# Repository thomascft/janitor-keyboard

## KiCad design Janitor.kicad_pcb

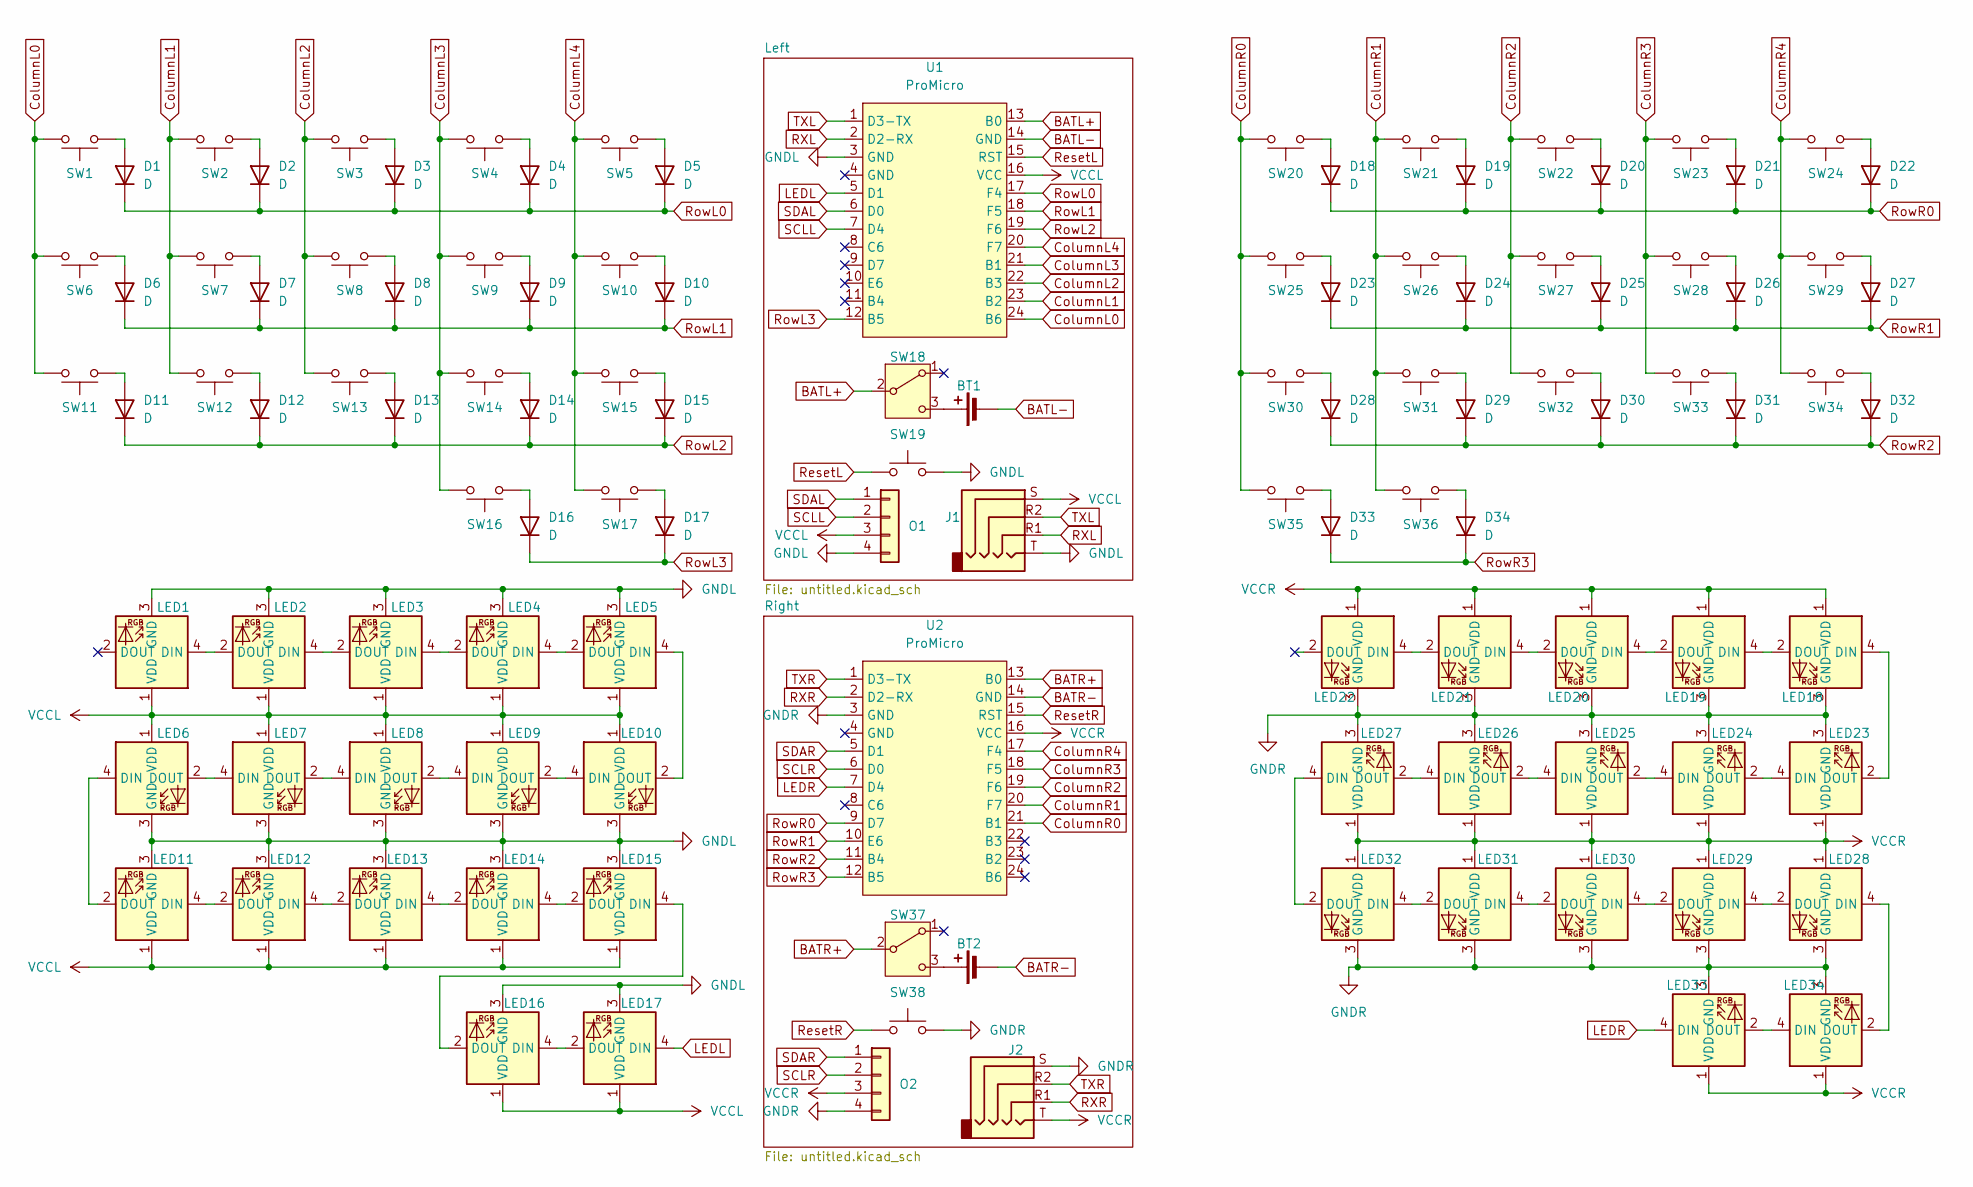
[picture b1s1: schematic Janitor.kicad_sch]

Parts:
BT1, BT2: Battery_Cell; CONN_Battery_JST
D1, D2, D3, D4, D5, D6, D7, D8, D9, D10, D11, D12, D13, D14, D15, D16, D17, D18, D19, D20, D21, D22, D23, D24, D25, D26, D27, D28, D29, D30, D31, D32, D33, D34: D; D_SOD-123
J1, J2: AudioJack4; TRRS-PJ-320A
LED1, LED2, LED3, LED4, LED5, LED6, LED7, LED8, LED9, LED10, LED11, LED12, LED13, LED14, LED15, LED16, LED17, LED18, LED19, LED20, LED21, LED22, LED23, LED24, LED25, LED26, LED27, LED28, LED29, LED30, LED31, LED32, LED33, LED34: SK6812MINI-E; LED_SK6812-Mini-E
O1, O2: Conn_01x04; OLED_SSD1306_128x32
SW1, SW2, SW3, SW4, SW5, SW6, SW7, SW8, SW9, SW10, SW11, SW12, SW13, SW14, SW15, SW16, SW17, SW20, SW21, SW22, SW23, SW24, SW25, SW26, SW27, SW28, SW29, SW30, SW31, SW32, SW33, SW34, SW35, SW36: SW_Push; SW_Choc_Hotswap
SW18, SW37: SW_SPDT; SW_SPDT_PCM12
SW19, SW38: SW_Push; Panasonic_EVQPUL_EVQPUC
U1, U2: ProMicro; SuperMini_nRF52840

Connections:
BATL+: SW18.2 (B), U1.13 (B0)
BATL-: BT1.2 (-), U1.14 (GND)
BATR+: SW37.2 (B), U2.13 (B0)
BATR-: BT2.2 (-), U2.14 (GND)
ColumnL0: SW1.2, SW6.2, SW11.2, U1.24 (B6)
ColumnL1: SW2.2, SW7.2, SW12.2, U1.23 (B2)
ColumnL2: SW3.2, SW8.2, SW13.2, U1.22 (B3)
ColumnL3: SW4.2, SW9.2, SW14.2, SW16.2, U1.21 (B1)
ColumnL4: SW5.2, SW10.2, SW15.2, SW17.2, U1.20 (F7)
ColumnR0: SW20.2, SW25.2, SW30.2, SW35.2, U2.21 (B1)
ColumnR1: SW21.2, SW26.2, SW31.2, SW36.2, U2.20 (F7)
ColumnR2: SW22.2, SW27.2, SW32.2, U2.19 (F6)
ColumnR3: SW23.2, SW28.2, SW33.2, U2.18 (F5)
ColumnR4: SW24.2, SW29.2, SW34.2, U2.17 (F4)
GNDL: J1.T, LED1.3 (GND), LED2.3 (GND), LED3.3 (GND), LED4.3 (GND), LED5.3 (GND), LED6.3 (GND), LED7.3 (GND), LED8.3 (GND), LED9.3 (GND), LED10.3 (GND), LED11.3 (GND), LED12.3 (GND), LED13.3 (GND), LED14.3 (GND), LED15.3 (GND), LED16.3 (GND), LED17.3 (GND), O1.4, SW19.2, U1.3 (GND)
GNDR: J2.S, LED18.3 (GND), LED19.3 (GND), LED20.3 (GND), LED21.3 (GND), LED22.3 (GND), LED23.3 (GND), LED24.3 (GND), LED25.3 (GND), LED26.3 (GND), LED27.3 (GND), LED28.3 (GND), LED29.3 (GND), LED30.3 (GND), LED31.3 (GND), LED32.3 (GND), LED33.3 (GND), LED34.3 (GND), O2.4, SW38.2, U2.3 (GND)
LEDL: LED17.4 (DIN), U1.5 (D1)
LEDR: LED33.4 (DIN), U2.7 (D4)
unnamed: BT1.1 (+), SW18.3 (C)
unnamed: BT2.1 (+), SW37.3 (C)
unnamed: D1.2 (A), SW1.1
unnamed: D2.2 (A), SW2.1
unnamed: D3.2 (A), SW3.1
unnamed: D4.2 (A), SW4.1
unnamed: D5.2 (A), SW5.1
unnamed: D6.2 (A), SW6.1
unnamed: D7.2 (A), SW7.1
unnamed: D8.2 (A), SW8.1
unnamed: D9.2 (A), SW9.1
unnamed: D10.2 (A), SW10.1
unnamed: D11.2 (A), SW11.1
unnamed: D12.2 (A), SW12.1
unnamed: D13.2 (A), SW13.1
unnamed: D14.2 (A), SW14.1
unnamed: D15.2 (A), SW15.1
unnamed: D16.2 (A), SW16.1
unnamed: D17.2 (A), SW17.1
unnamed: D18.2 (A), SW20.1
unnamed: D19.2 (A), SW21.1
unnamed: D20.2 (A), SW22.1
unnamed: D21.2 (A), SW23.1
unnamed: D22.2 (A), SW24.1
unnamed: D23.2 (A), SW25.1
unnamed: D24.2 (A), SW26.1
unnamed: D25.2 (A), SW27.1
unnamed: D26.2 (A), SW28.1
unnamed: D27.2 (A), SW29.1
unnamed: D28.2 (A), SW30.1
unnamed: D29.2 (A), SW31.1
unnamed: D30.2 (A), SW32.1
unnamed: D31.2 (A), SW33.1
unnamed: D32.2 (A), SW34.1
unnamed: D33.2 (A), SW35.1
unnamed: D34.2 (A), SW36.1
unnamed: LED1.4 (DIN), LED2.2 (DOUT)
unnamed: LED2.4 (DIN), LED3.2 (DOUT)
unnamed: LED3.4 (DIN), LED4.2 (DOUT)
unnamed: LED4.4 (DIN), LED5.2 (DOUT)
unnamed: LED6.2 (DOUT), LED7.4 (DIN)
unnamed: LED7.2 (DOUT), LED8.4 (DIN)
unnamed: LED8.2 (DOUT), LED9.4 (DIN)
unnamed: LED9.2 (DOUT), LED10.4 (DIN)
unnamed: LED5.4 (DIN), LED10.2 (DOUT)
unnamed: LED11.4 (DIN), LED12.2 (DOUT)
unnamed: LED6.4 (DIN), LED11.2 (DOUT)
unnamed: LED12.4 (DIN), LED13.2 (DOUT)
unnamed: LED13.4 (DIN), LED14.2 (DOUT)
unnamed: LED14.4 (DIN), LED15.2 (DOUT)
unnamed: LED15.4 (DIN), LED16.2 (DOUT)
unnamed: LED16.4 (DIN), LED17.2 (DOUT)
unnamed: LED18.4 (DIN), LED23.2 (DOUT)
unnamed: LED18.2 (DOUT), LED19.4 (DIN)
unnamed: LED19.2 (DOUT), LED20.4 (DIN)
unnamed: LED20.2 (DOUT), LED21.4 (DIN)
unnamed: LED21.2 (DOUT), LED22.4 (DIN)
unnamed: LED23.4 (DIN), LED24.2 (DOUT)
unnamed: LED24.4 (DIN), LED25.2 (DOUT)
unnamed: LED25.4 (DIN), LED26.2 (DOUT)
unnamed: LED26.4 (DIN), LED27.2 (DOUT)
unnamed: LED27.4 (DIN), LED32.2 (DOUT)
unnamed: LED28.4 (DIN), LED34.2 (DOUT)
unnamed: LED28.2 (DOUT), LED29.4 (DIN)
unnamed: LED29.2 (DOUT), LED30.4 (DIN)
unnamed: LED30.2 (DOUT), LED31.4 (DIN)
unnamed: LED31.2 (DOUT), LED32.4 (DIN)
unnamed: LED33.2 (DOUT), LED34.4 (DIN)
RXL: J1.R1, U1.2 (D2-RX)
RXR: J2.R1, U2.2 (D2-RX)
ResetL: SW19.1, U1.15 (RST)
ResetR: SW38.1, U2.15 (RST)
RowL0: D1.1 (K), D2.1 (K), D3.1 (K), D4.1 (K), D5.1 (K), U1.17 (F4)
RowL1: D6.1 (K), D7.1 (K), D8.1 (K), D9.1 (K), D10.1 (K), U1.18 (F5)
RowL2: D11.1 (K), D12.1 (K), D13.1 (K), D14.1 (K), D15.1 (K), U1.19 (F6)
RowL3: D16.1 (K), D17.1 (K), U1.12 (B5)
RowR0: D18.1 (K), D19.1 (K), D20.1 (K), D21.1 (K), D22.1 (K), U2.9 (D7)
RowR1: D23.1 (K), D24.1 (K), D25.1 (K), D26.1 (K), D27.1 (K), U2.10 (E6)
RowR2: D28.1 (K), D29.1 (K), D30.1 (K), D31.1 (K), D32.1 (K), U2.11 (B4)
RowR3: D33.1 (K), D34.1 (K), U2.12 (B5)
SCLL: O1.2, U1.7 (D4)
SCLR: O2.2, U2.6 (D0)
SDAL: O1.1, U1.6 (D0)
SDAR: O2.1, U2.5 (D1)
TXL: J1.R2, U1.1 (D3-TX)
TXR: J2.R2, U2.1 (D3-TX)
VCCL: J1.S, LED1.1 (VDD), LED2.1 (VDD), LED3.1 (VDD), LED4.1 (VDD), LED5.1 (VDD), LED6.1 (VDD), LED7.1 (VDD), LED8.1 (VDD), LED9.1 (VDD), LED10.1 (VDD), LED11.1 (VDD), LED12.1 (VDD), LED13.1 (VDD), LED14.1 (VDD), LED15.1 (VDD), LED16.1 (VDD), LED17.1 (VDD), O1.3, U1.16 (VCC)
VCCR: J2.T, LED18.1 (VDD), LED19.1 (VDD), LED20.1 (VDD), LED21.1 (VDD), LED22.1 (VDD), LED23.1 (VDD), LED24.1 (VDD), LED25.1 (VDD), LED26.1 (VDD), LED27.1 (VDD), LED28.1 (VDD), LED29.1 (VDD), LED30.1 (VDD), LED31.1 (VDD), LED32.1 (VDD), LED33.1 (VDD), LED34.1 (VDD), O2.3, U2.16 (VCC)

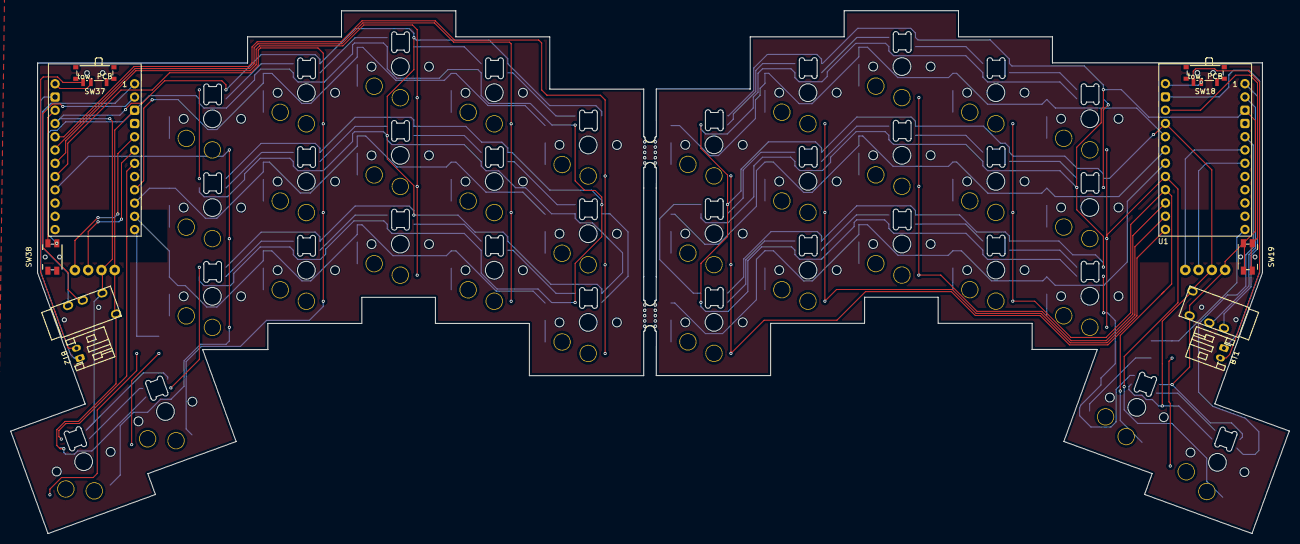
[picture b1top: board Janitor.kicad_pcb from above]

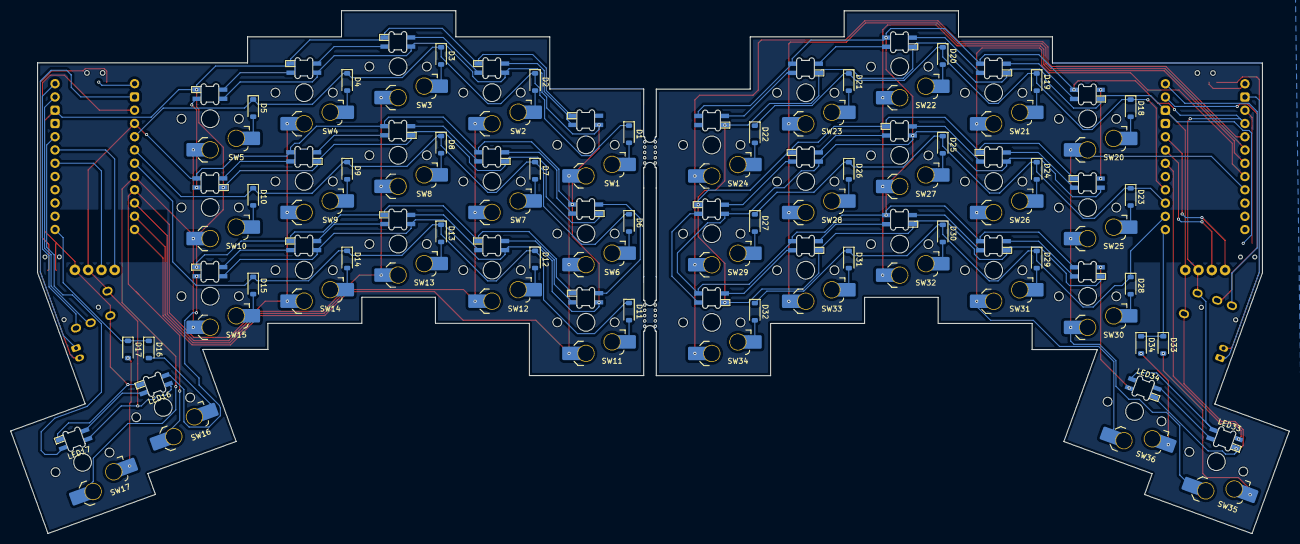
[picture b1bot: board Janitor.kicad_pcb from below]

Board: 2 copper layers, 245.0 x 100.2 mm, 114 parts (68 on the bottom side), 106 nets.

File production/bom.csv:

Designator,Footprint,Quantity,Value,LCSC Part #
"BT1, BT2",CONN_Battery_JST,2,Battery_Cell,
"D1, D10, D11, D12, D13, D14, D15, D16, D17, D18, D19, D2, D20, D21, D22, D23, D24, D25, D26, D27, D28, D29, D3, D30, D31, D32, D33, D34, D4, D5, D6, D7, D8, D9",D_SOD-123,34,D,
"J1, J2",TRRS-PJ-320A,2,AudioJack4,
"LED1, LED10, LED11, LED12, LED13, LED14, LED15, LED16, LED17, LED18, LED19, LED2, LED20, LED21, LED22, LED23, LED24, LED25, LED26, LED27, LED28, LED29, LED3, LED30, LED31, LED32, LED33, LED34, LED4, LED5, LED6, LED7, LED8, LED9",LED_SK6812-Mini-E,34,SK6812MINI-E,
"O1, O2",OLED_SSD1306_128x32,2,Conn_01x04,
"SW1, SW10, SW11, SW12, SW13, SW14, SW15, SW16, SW17, SW2, SW20, SW21, SW22, SW23, SW24, SW25, SW26, SW27, SW28, SW29, SW3, SW30, SW31, SW32, SW33, SW34, SW35, SW36, SW4, SW5, SW6, SW7, SW8, SW9",SW_Choc_Hotswap,34,SW_Push,
"SW18, SW37",SW_SPDT_PCM12,2,SW_SPDT,
"SW19, SW38",Panasonic_EVQPUL_EVQPUC,2,SW_Push,

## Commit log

2024-11-27 Checkpoint
2024-11-27 Cleaned up a little
2024-11-27 Removed production export
